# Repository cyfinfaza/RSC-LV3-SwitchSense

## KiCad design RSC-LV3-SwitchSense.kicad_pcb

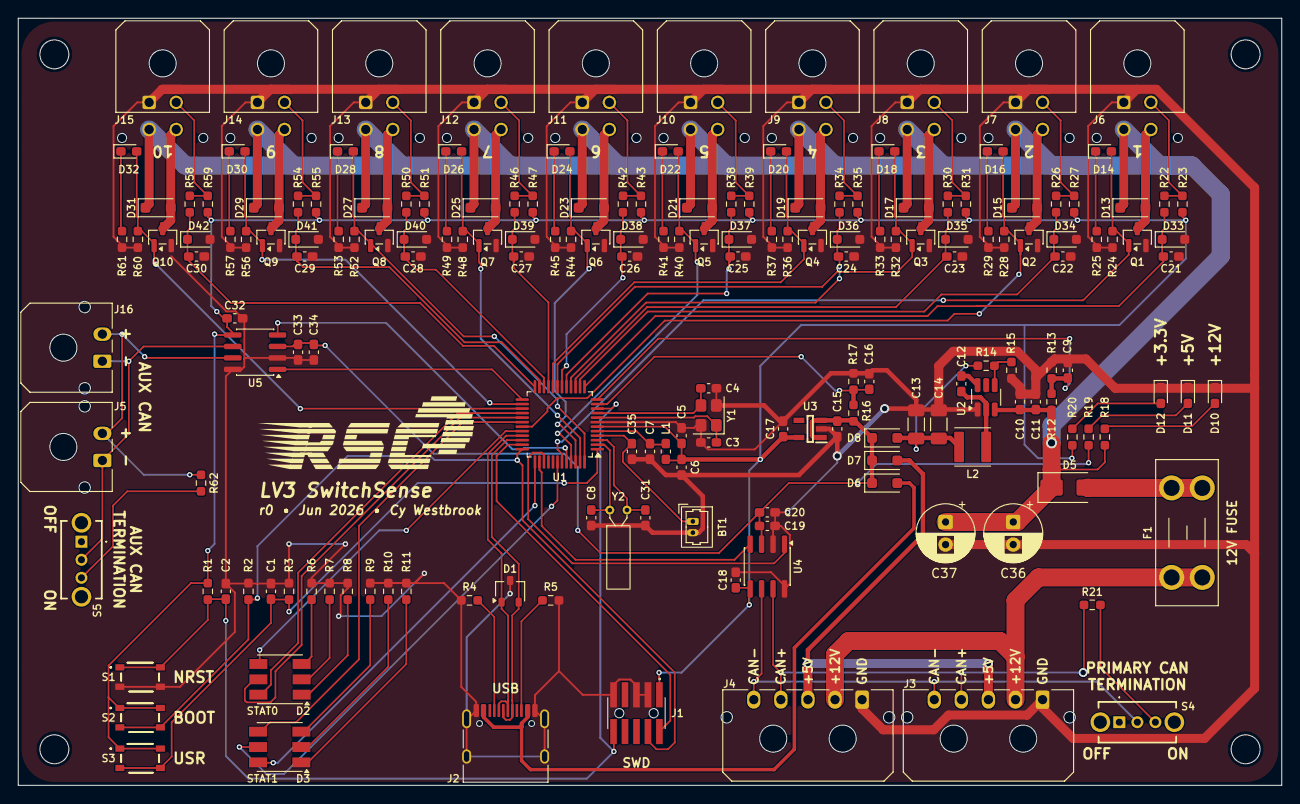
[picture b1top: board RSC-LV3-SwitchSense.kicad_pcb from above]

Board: 2 copper layers, 140.0 x 85.0 mm, 181 parts (0 on the bottom side), 103 nets.

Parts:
BT1: Molex 53047-0210; Molex_PicoBlade_53047-0210_1x02_P1.25mm_Vertical
C1, C2, C5, C9, C12, C16, C18, C19, C21, C22, C23, C24, C25, C26, C27, C28, C29, C30, C32, C33: 100n; C_0603_1608Metric_Pad1.08x0.95mm_HandSolder
C3, C4, C8, C31: 6.8p; C_0603_1608Metric_Pad1.08x0.95mm_HandSolder
C6, C7, C15, C17, C20, C34, C35: 1u; C_0603_1608Metric_Pad1.08x0.95mm_HandSolder
C10, C11: 2.2u; C_0603_1608Metric_Pad1.08x0.95mm_HandSolder
C13, C14: 22u; C_1206_3216Metric_Pad1.33x1.80mm_HandSolder
C36, C37: 100u; CP_Radial_D6.3mm_P2.50mm
D1: PESD2USB3UV; SOT-23W
D2, D3: LED_RGB; LED_RGB_5050-6
D5: D_Schottky; D_SMA
D6, D7, D8, D13, D15, D17, D19, D21, D23, D25, D27, D29, D31: D_Schottky; D_SOD-123F
D10, D11, D12, D14, D16, D18, D20, D22, D24, D26, D28, D30, D32: LED; LED_0603_1608Metric_Pad1.05x0.95mm_HandSolder
D33, D34, D35, D36, D37, D38, D39, D40, D41, D42: D_Zener; D_SOD-323_HandSoldering
F1: Fuse; Fuseholder_Blade_Mini_Keystone_3568
J1: FTSH-105-01-L-DV-K-A; FTSH-105-XX-YYY-DV-K-A
J2: USB_C_Receptacle_USB2.0_16P; USB_C_Receptacle_HRO_TYPE-C-31-M-12
J3, J4: Molex 43650-0500; Molex_Micro-Fit_3.0_43650-0500_1x05_P3.00mm_Horizontal_Vert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
J5, J16: Molex 43650-0200; Molex_Micro-Fit_3.0_43650-0200_1x02_P3.00mm_Horizontal_Vert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
J6, J7, J8, J9, J10, J11, J12, J13, J14, J15: Molex 43045-0400; Molex_Micro-Fit_3.0_43045-0400_2x02_P3.00mm_Horizontal_Vert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
L1: L_Ferrite; L_0603_1608Metric_Pad1.05x0.95mm_HandSolder
L2: 8.2u; L_Abracon_ASPI-4030S
Q1, Q2, Q3, Q4, Q5, Q6, Q7, Q8, Q9, Q10: AO3400A; SOT-23
R1, R2, R3, R4, R5, R13, R22, R23, R24, R26, R27, R28, R30, R31, R32, R34, R35, R36, R38, R39, R40, R42, R43, R44, R46, R47, R48, R50, R51, R52, R54, R55, R56, R58, R59, R60: 5.1k; R_0603_1608Metric_Pad0.98x0.95mm_HandSolder
R6, R7, R9, R10: 50; R_0603_1608Metric_Pad0.98x0.95mm_HandSolder
R8, R11, R20, R21, R62: 120; R_0603_1608Metric_Pad0.98x0.95mm_HandSolder
R12, R14, R16, R17: 100k; R_0603_1608Metric_Pad0.98x0.95mm_HandSolder
R15: 12.7k; R_0603_1608Metric_Pad0.98x0.95mm_HandSolder
R18: 2.2k; R_0603_1608Metric_Pad0.98x0.95mm_HandSolder
R19, R25, R29, R33, R37, R41, R45, R49, R53, R57, R61: 470; R_0603_1608Metric_Pad0.98x0.95mm_HandSolder
S1, S2, S3: RKB2SJM250SMTR_LFS; RKB2SJM250SMTRLFS
S4, S5: SLW-864587-2A-RA-N-D; SLW8645872ARAND
U1: STM32G0B1CBTx; LQFP-48_7x7mm_P0.5mm
U2: TPS54302; SOT-23-6_Handsoldering
U3: TLV74033PDBVR; SOT95P280X145-5N
U4, U5: TJA1051T-3; SOIC-8_3.9x4.9mm_P1.27mm
Y1: Crystal_GND24; Crystal_SMD_3225-4Pin_3.2x2.5mm
Y2: 32.768 kHz 6pF; Crystal_C26-LF_D2.1mm_L6.5mm_Horizontal

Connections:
+3.3V: C5.1, C6.1, C17.1, C18.1, C32.1, J1.1, L1.1, R1.2, R20.1, R23.1, R27.1, R31.1, R35.1, R39.1, R43.1, R47.1, R51.1, R55.1, R59.1, S2.1 (COM_1), S2.2 (COM_2), S3.1 (COM_1), S3.2 (COM_2), U1.6 (VDD), U3.5 (OUT), U4.5 (VIO), U5.5 (VIO)
+5V: C15.1, C19.1, C20.1, C33.1, C34.1, D6.1 (K), D7.1 (K), D8.1 (K), R16.1, R19.1, U3.1 (IN), U3.3 (EN), U4.3 (VCC), U5.3 (VCC)
+5V_BUCK: C13.1, C14.1, D8.2 (A), L2.2, R14.1
+5V_BUS: D7.2 (A), J3.3, J4.3
+5V_USB: D6.2 (A), J2.A4 (VBUS), J2.A9 (VBUS), J2.B4 (VBUS), J2.B9 (VBUS)
+12V: C10.1, C11.1, C36.1, C37.1, D5.1 (K), D13.1 (K), D15.1 (K), D17.1 (K), D19.1 (K), D21.1 (K), D23.1 (K), D25.1 (K), D27.1 (K), D29.1 (K), D31.1 (K), J6.3, J7.3, J8.3, J9.3, J10.3, J11.3, J12.3, J13.3, J14.3, J15.3, R12.1, R18.1, U2.3 (VIN)
+12V_IN: F1.1, J3.2, J4.2
+VDDA: C7.1, L1.2, U1.5 (VREF+)
AUX_CAN+: J5.2, J16.2, R62.1, U5.7 (CANH)
AUX_CAN-: J5.1, J16.1, S5.2 (COM), U5.6 (CANL)
BOOT0: J1.4, R2.2, S2.3 (NO_1), S2.4 (NO_2), U1.36 (PA14)
BTN_USR1: C1.1, R3.2, S3.3 (NO_1), S3.4 (NO_2), U1.1 (PC13)
FDCAN1_RX: U1.38 (PD0), U4.4 (RXD)
FDCAN1_TX: U1.39 (PD1), U4.1 (TXD)
FDCAN2_RX: U1.44 (PB5), U5.4 (RXD)
FDCAN2_TX: U1.25 (PB13), U5.1 (TXD)
GND: BT1.2 (-), C1.2, C2.2, C3.2, C4.2, C5.2, C6.2, C7.2, C8.2, C9.2, C10.2, C11.2, C13.2, C14.2, C15.2, C16.2, C17.2, C18.2, C19.2, C20.2, C21.2, C22.2, C23.2, C24.2, C25.2, C26.2, C27.2, C28.2, C29.2, C30.2, C31.2, C32.2, C33.2, C34.2, C35.2, C36.2, C37.2, D1.3 (A), D10.1 (K), D11.1 (K), D12.1 (K), D33.2 (A), D34.2 (A), D35.2 (A), D36.2 (A), D37.2 (A), D38.2 (A), D39.2 (A), D40.2 (A), D41.2 (A), D42.2 (A), J1.3, J1.5, J1.9, J2.A1 (GND), J2.A12 (GND), J2.B1 (GND), J2.B12 (GND), J2.SH, J3.1, J4.1, J6.1, J7.1, J8.1, J9.1, J10.1, J11.1, J12.1, J13.1, J14.1, J15.1, Q1.2 (S), Q2.2 (S), Q3.2 (S), Q4.2 (S), Q5.2 (S), Q6.2 (S), Q7.2 (S), Q8.2 (S), Q9.2 (S), Q10.2 (S), R2.1, R3.1, R4.1, R5.1, R6.1, R7.1, R8.1, R9.1, R10.1, R11.1, R13.2, R15.2, R17.2, R24.2, R25.2, R28.2, R29.2, R32.2, R33.2, R36.2, R37.2, R40.2, R41.2, R44.2, R45.2, R48.2, R49.2, R52.2, R53.2, R56.2, R57.2, R60.2, R61.2, S1.3 (NO_1), S1.4 (NO_2), U1.7 (VSS), U2.1 (GND), U3.2 (GND), U4.2 (GND), U4.8 (S), U5.2 (GND), U5.8 (S), Y1.2, Y1.4
HSE_IN: C3.1, U1.8 (PF0), Y1.1
HSE_OUT: C4.1, U1.9 (PF1), Y1.3
IN_1: C21.1, D33.1 (K), R22.1, U1.13 (PA2)
IN_2: C22.1, D34.1 (K), R26.1, U1.14 (PA3)
IN_3: C23.1, D35.1 (K), R30.1, U1.15 (PA4)
IN_4: C24.1, D36.1 (K), R34.1, U1.16 (PA5)
IN_5: C25.1, D37.1 (K), R38.1, U1.17 (PA6)
IN_6: C26.1, D38.1 (K), R42.1, U1.18 (PA7)
IN_7: C27.1, D39.1 (K), R46.1, U1.21 (PB2)
IN_8: C28.1, D40.1 (K), R50.1, U1.22 (PB10)
IN_9: C29.1, D41.1 (K), R54.1, U1.23 (PB11)
IN_10: C30.1, D42.1 (K), R58.1, U1.24 (PB12)
LSE_IN: C8.1, U1.2 (PC14), Y2.1
LSE_OUT: C31.1, U1.3 (PC15), Y2.2
NRST: C2.1, J1.10, R1.1, S1.1 (COM_1), S1.2 (COM_2), U1.10 (PF2)
unnamed: BT1.1 (+), C35.1, U1.4 (VBAT)
unnamed: D2.3 (BK), R6.2
unnamed: D2.2 (GK), R7.2
unnamed: D2.1 (RK), R8.2
unnamed: D3.3 (BK), R9.2
unnamed: D3.2 (GK), R10.2
unnamed: D3.1 (RK), R11.2
unnamed: D5.2 (A), F1.2
unnamed: D10.2 (A), R18.2
unnamed: D11.2 (A), R19.2
unnamed: D12.2 (A), R20.2
unnamed: D13.2 (A), J6.4, Q1.3 (D)
unnamed: D14.1 (K), R25.1
unnamed: D15.2 (A), J7.4, Q2.3 (D)
unnamed: D16.1 (K), R29.1
unnamed: D17.2 (A), J8.4, Q3.3 (D)
unnamed: D18.1 (K), R33.1
unnamed: D19.2 (A), J9.4, Q4.3 (D)
unnamed: D20.1 (K), R37.1
unnamed: D21.2 (A), J10.4, Q5.3 (D)
unnamed: D22.1 (K), R41.1
unnamed: D23.2 (A), J11.4, Q6.3 (D)
unnamed: D24.1 (K), R45.1
unnamed: D25.2 (A), J12.4, Q7.3 (D)
unnamed: D26.1 (K), R49.1
unnamed: D27.2 (A), J13.4, Q8.3 (D)
unnamed: D28.1 (K), R53.1
unnamed: D29.2 (A), J14.4, Q9.3 (D)
unnamed: D30.1 (K), R57.1
unnamed: D31.2 (A), J15.4, Q10.3 (D)
unnamed: D32.1 (K), R61.1
unnamed: J2.A5 (CC1), R4.2
unnamed: J2.B5 (CC2), R5.2
unnamed: J6.2, R22.2, R23.2
unnamed: J7.2, R26.2, R27.2
unnamed: J8.2, R30.2, R31.2
unnamed: J9.2, R34.2, R35.2
unnamed: J10.2, R38.2, R39.2
unnamed: J11.2, R42.2, R43.2
unnamed: J12.2, R46.2, R47.2
unnamed: J13.2, R50.2, R51.2
unnamed: J14.2, R54.2, R55.2
unnamed: J15.2, R58.2, R59.2
unnamed: R21.2, S4.3 (NO)
unnamed: R62.2, S5.3 (NO)
unnamed: C12.1, U2.6 (BOOT)
unnamed: R14.2, R15.1, U2.4 (FB)
unnamed: C12.2, L2.1, U2.2 (SW)
OUT_1: D14.2 (A), Q1.1 (G), R24.1, U1.43 (PB4)
OUT_2: D16.2 (A), Q2.1 (G), R28.1, U1.31 (PC7)
OUT_3: D18.2 (A), Q3.1 (G), R32.1, U1.19 (PB0)
OUT_4: D20.2 (A), Q4.1 (G), R36.1, U1.20 (PB1)
OUT_5: D22.2 (A), Q5.1 (G), R40.1, U1.45 (PB6)
OUT_6: D24.2 (A), Q6.1 (G), R44.1, U1.46 (PB7)
OUT_7: D26.2 (A), Q7.1 (G), R48.1, U1.47 (PB8)
OUT_8: D28.2 (A), Q8.1 (G), R52.1, U1.48 (PB9)
OUT_9: D30.2 (A), Q9.1 (G), R56.1, U1.26 (PB14)
OUT_10: D32.2 (A), Q10.1 (G), R60.1, U1.27 (PB15)
PRIMARY_CAN+: J3.4, J4.4, R21.1, U4.7 (CANH)
PRIMARY_CAN-: J3.5, J4.5, S4.2 (COM), U4.6 (CANL)
STAT0_B: D2.4 (BA), U1.32 (PA10/UCPD1_DBCC2)
STAT0_G: D2.5 (GA), U1.29 (PA9/UCPD1_DBCC1)
STAT0_R: D2.6 (RA), U1.28 (PA8)
STAT1_B: D3.4 (BA), U1.30 (PC6)
STAT1_G: D3.5 (GA), U1.42 (PB3)
STAT1_R: D3.6 (RA), U1.37 (PA15)
SWD_IO: J1.2, U1.35 (PA13)
USB+: D1.2 (K), J2.A6 (D+), J2.B6 (D+), U1.34 (PA10/PA12)
USB-: D1.1 (K), J2.A7 (D-), J2.B7 (D-), U1.33 (PA9/PA11)
V_SENSE_5: C16.1, R16.2, R17.1, U1.11 (PA0)
V_SENSE_12: C9.1, R12.2, R13.1, U1.12 (PA1)

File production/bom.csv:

Designator,Footprint,Quantity,Value,LCSC Part #
BT1,Molex_PicoBlade_53047-0210_1x02_P1.25mm_Vertical,1,Molex 53047-0210,
"C1, C12, C16, C18, C19, C2, C21, C22, C23, C24, C25, C26, C27, C28, C29, C30, C32, C33, C5, C9",0603,20,100n,
"C10, C11",0603,2,2.2u,
"C13, C14",1206,2,22u,
"C15, C17, C20, C34, C35, C6, C7",0603,7,1u,
"C3, C31, C4, C8",0603,4,6.8p,
"C36, C37",CP_Radial_D6.3mm_P2.50mm,2,100u,
D1,SOT-23W,1,PESD2USB3UV,
"D10, D11, D12, D14, D16, D18, D20, D22, D24, D26, D28, D30, D32",0603,13,LED,
"D13, D15, D17, D19, D21, D23, D25, D27, D29, D31, D6, D7, D8",D_SOD-123F,13,D_Schottky,
"D2, D3",LED_RGB_5050-6,2,LED_RGB,
"D33, D34, D35, D36, D37, D38, D39, D40, D41, D42",D_SOD-323_HandSoldering,10,D_Zener,
D5,D_SMA,1,D_Schottky,
F1,Fuseholder_Blade_Mini_Keystone_3568,1,Fuse,
J1,FTSH-105-XX-YYY-DV-K-A,1,FTSH-105-01-L-DV-K-A,
"J10, J11, J12, J13, J14, J15, J6, J7, J8, J9",Molex_Micro-Fit_3.0_43045-0400_2x02_P3.00mm_Horizontal_VerticalCompatible,10,Molex 43045-0400,
"J16, J5",Molex_Micro-Fit_3.0_43650-0200_1x02_P3.00mm_Horizontal_VerticalCompatible,2,Molex 43650-0200,
J2,USB_C_Receptacle_HRO_TYPE-C-31-M-12,1,USB_C_Receptacle_USB2.0_16P,
"J3, J4",Molex_Micro-Fit_3.0_43650-0500_1x05_P3.00mm_Horizontal_VerticalCompatible,2,Molex 43650-0500,
L1,0603,1,L_Ferrite,
L2,L_Abracon_ASPI-4030S,1,8.2u,
"Q1, Q10, Q2, Q3, Q4, Q5, Q6, Q7, Q8, Q9",SOT-23,10,AO3400A,
"R1, R13, R2, R22, R23, R24, R26, R27, R28, R3, R30, R31, R32, R34, R35, R36, R38, R39, R4, R40, R42, R43, R44, R46, R47, R48, R5, R50, R51, R52, R54, R55, R56, R58, R59, R60",0603,36,5.1k,
"R10, R6, R7, R9",0603,4,50,
"R11, R20, R21, R62, R8",0603,5,120,
"R12, R14, R16, R17",0603,4,100k,
R15,0603,1,12.7k,
R18,0603,1,2.2k,
"R19, R25, R29, R33, R37, R41, R45, R49, R53, R57, R61",0603,11,470,
"S1, S2, S3",RKB2SJM250SMTRLFS,3,RKB2SJM250SMTR_LFS,
"S4, S5",SLW8645872ARAND,2,SLW-864587-2A-RA-N-D,
U1,LQFP-48_7x7mm_P0.5mm,1,STM32G0B1CBTx,
U2,SOT-23-6_Handsoldering,1,TPS54302,
U3,SOT95P280X145-5N,1,TLV74033PDBVR,
"U4, U5",SOIC-8_3.9x4.9mm_P1.27mm,2,TJA1051T-3,
Y1,Crystal_SMD_3225-4Pin_3.2x2.5mm,1,Crystal_GND24,
Y2,Crystal_C26-LF_D2.1mm_L6.5mm_Horizontal,1,32.768 kHz 6pF,

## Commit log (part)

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2026-06-22 r0 final
